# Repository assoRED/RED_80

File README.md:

# RED_80 computer

Currently **work in progress.**

# Repository content

# BOM

 - CMOS z80 CPU
 - AS6c62256 32k*8bits CMOS low power SRAM
 - CMOS 4011 quad NAND logic gate
 - CMOS 4071 quad OR logic gate
 - CMOS 40106 hex trigger
 - 1x tactile switch
 - 3x poalized electrolytic 0.01uF capacitor
 - 2x ceramic (unpolarized) 22pF capactitor
 - Crystal (freq. TBD)
 - 1x 10k resistror
 - 1x 1M resistor
 
# Memory map

| memory address | Usage |
|       :---:    |  :---:  |
|`0x0000` - `0x1FFF`|ROM |
|`0x2000` - `0x3FFF`|EXT ROM| 
|`0x8000` - `0xFFFF`|RAM |

# ROM content

 - `0x0000` system reset/init
 - memroy monitor
 
 # Serial interface
 
 System has been designed to be interfaced with a French Minitel 1B made by MATRA communication terminal.
 
 Serial output is slow (by design). Serial interface configuration : 
 
 - 4800 baud
 - 7bit DATA
 - 1bit STOP
 - Even parity
 - No flow control
 
 To be able to use, you need to setup the minitel in the right comunication mode. Do in order
 
 1) `Fonction`+`T`, `A` Activate "Péri-Informatique" mode
 2) `Fonction`+`T`, `E` Deactivate local character echo
 3) `Fonction`+`P`, `4` Set baudrate to 4800

 Minitel interface can be adapted to serial using the [assoRED/MinitelInterface](https://github.com/assoRED/MinitelInterface) circuit

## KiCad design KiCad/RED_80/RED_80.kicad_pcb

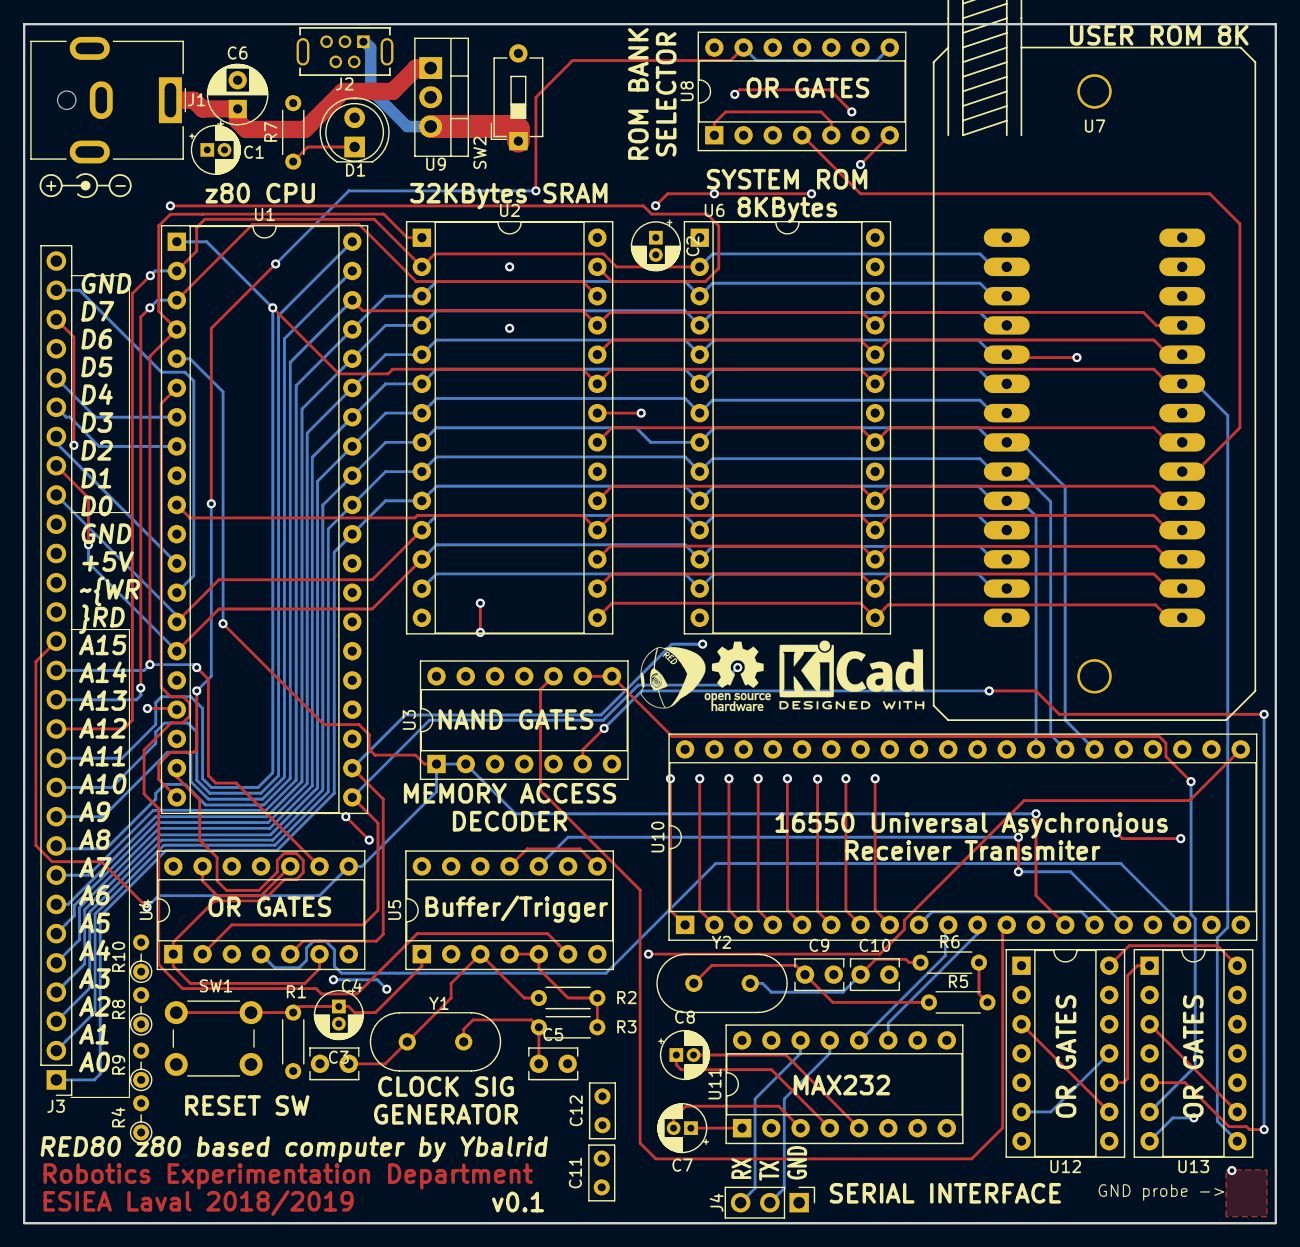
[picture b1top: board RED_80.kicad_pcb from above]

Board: 4 copper layers, 108.7 x 104.1 mm, 44 parts (0 on the bottom side), 78 nets.

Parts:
C1, C2: 0.01uF; CP_Radial_D4.0mm_P1.50mm
C3: 0.01uf; CP_Radial_D4.0mm_P1.50mm
C4, C5, C9, C10: 22pF; C_Rect_L4.0mm_W2.5mm_P2.50mm
C6: 100nf; CP_Radial_D5.0mm_P2.50mm
C7, C8: CP; CP_Radial_D4.0mm_P1.50mm
C11, C12: C; C_Rect_L4.6mm_W2.0mm_P2.50mm_MKS02_FKP02
D1: LED; LED_D5.0mm
J1: Barrel_Jack; BarrelJack_CUI_PJ-063AH_Horizontal
J2: USB_B_Micro; USB_Micro-B_Tensility_54-00023_Vertical
J3: Conn_01x29_Male; PinHeader_1x29_P2.54mm_Vertical
J4: Conn_01x03_Male; PinHeader_1x03_P2.54mm_Vertical
R1: 10k; R_Axial_DIN0204_L3.6mm_D1.6mm_P5.08mm_Horizontal
R2, R5: 1M; R_Axial_DIN0204_L3.6mm_D1.6mm_P5.08mm_Horizontal
R3, R6: R; R_Axial_DIN0204_L3.6mm_D1.6mm_P5.08mm_Horizontal
R4, R8, R9, R10: 100k; R_Axial_DIN0204_L3.6mm_D1.6mm_P2.54mm_Vertical
R7: 180; R_Axial_DIN0204_L3.6mm_D1.6mm_P5.08mm_Horizontal
SW1: RESET_SW; SW_PUSH_6mm_H4.3mm
SW2: SW_SPST; SW_DIP_SPSTx01_Slide_6.7x4.1mm_W7.62mm_P2.54mm_LowProfile
U1: Z80CPU; DIP-40_W15.24mm_Socket
U2: AS6C62256; DIP-28_W15.24mm_Socket
U3: 4011; DIP-14_W7.62mm_Socket
U4, U8: 4071; DIP-14_W7.62mm_Socket
U5: 40106; DIP-14_W7.62mm_Socket
U6: 28C64; DIP-28_W15.24mm_Socket
U7: 28C64; 3M-TEXTOOL-ZIF-DIP-28
U9: L7805; TO-220-3_Vertical
U10: 16550; DIP-40_W15.24mm_Socket
U11: MAX232; DIP-16_W7.62mm_Socket
U12, U13: 4075; DIP-14_W7.62mm_Socket
Y1, Y2: Crystal; Crystal_HC18-U_Vertical

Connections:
/A0: J3.1, U1.30, U2.10, U6.11, U7.11, U10.28
/A1: J3.2, U1.31, U2.9, U6.12, U7.12, U10.27
/A2: J3.3, U1.32, U2.8, U6.13, U7.13, U10.26
/A3: J3.4, U1.33, U2.7, U6.15, U7.15, U12.1
/A4: J3.5, U1.34, U2.6, U6.16, U7.16, U12.2
/A5: J3.6, U1.35, U2.5, U6.17, U7.17, U12.8
/A6: J3.7, U1.36, U2.4, U6.18, U7.18, U12.4
/A7: J3.8, U1.37, U2.3, U6.19, U7.19, U12.5
/A8: J3.9, U1.38, U2.25, U12.12
/A9: J3.10, U1.39, U2.24, U12.13
/A10: J3.11, U1.40, U2.21, U13.2
/A11: J3.12, U1.1, U2.23, U13.8
/A12: J3.13, U1.2, U2.2, U13.4
/A13: J3.14, U1.3, U2.26, U13.5
/A14: J3.15, U1.4, U2.1, U10.13
/A15: J3.16, U1.5, U3.1, U3.2, U10.14
/CPU_BUSRQ: R4.2, U1.25
/CPU_INT: R9.2, U1.16
/CPU_NMI: R10.2, U1.17
/CPU_WAIT: R8.2, U1.24
/D0: J3.21, U1.14, U2.11, U6.10, U7.10, U10.1
/D1: J3.22, U1.15, U2.12, U6.9, U7.9, U10.2
/D2: J3.23, U1.12, U2.13, U6.8, U7.8, U10.3
/D3: J3.24, U1.8, U2.15, U6.7, U7.7, U10.4
/D4: J3.25, U1.7, U2.16, U6.6, U7.6, U10.5
/D5: J3.26, U1.9, U2.17, U6.5, U7.5, U10.6
/D6: J3.27, U1.10, U2.18, U6.4, U7.4, U10.7
/D7: J3.28, U1.13, U2.19, U6.3, U7.3, U10.8
/RED_80_PowerInput/DC+5: J2.1, SW2.1, U9.3
/RED_80_PowerInput/DC_IN: C6.1, J1.1, U9.1
/RED_80_Ram/RAM_ENABLE: U2.20, U3.3
/RED_80_Roms/A8: U6.25, U7.25
/RED_80_Roms/A9: U6.24, U7.24
/RED_80_Roms/A10: U6.21, U7.21
/RED_80_Roms/A11: U6.23, U7.23
/RED_80_Roms/A12: U6.2, U7.2
/RED_80_Roms/USER_ROM_SELECTED: U3.4, U8.6
/RED_80_SERIAL/SERIAL_CLOCK: U5.10, U10.16
CPU_CLK: U1.6, U5.6
GND: C1.2, C2.2, C3.2, C4.2, C5.2, C6.2, C9.2, C10.2, C12.2, J1.2, J2.5, J2.6, J3.20, J3.29, J4.1, R7.2, SW1.2, U1.29, U2.14, U3.7, U4.7, U5.7, U6.14, U6.22, U7.14, U7.22, U8.7, U9.2, U10.19, U10.20, U10.22, U10.25, U11.15, U12.7, U13.7
MAIN_5V: C1.1, C2.1, C11.2, D1.2, J3.19, R1.1, R4.1, R8.1, R9.1, R10.1, SW2.2, U1.11, U2.28, U3.14, U4.14, U5.14, U6.27, U6.28, U7.27, U7.28, U8.14, U10.40, U11.16, U12.14, U13.14
unnamed: C3.1, R1.2, SW1.1, U5.1
unnamed: C4.1, R2.2, U5.3, Y1.1
unnamed: C5.1, R3.2, Y1.2
unnamed: C7.1, U11.1
unnamed: C7.2, U11.3
unnamed: C8.1, U11.4
unnamed: C8.2, U11.5
unnamed: C9.1, R5.2, U5.9, Y2.1
unnamed: C10.1, R6.2, Y2.2
unnamed: C11.1, U11.2
unnamed: C12.1, U11.6
unnamed: D1.1, R7.1
unnamed: R2.1, R3.1, U5.4, U5.5
unnamed: R5.1, R6.1, U5.8, U5.11
unnamed: U1.19, U4.1, U4.6
unnamed: U1.20, U8.8, U8.13
unnamed: U1.21, U4.2, U8.9
unnamed: U1.22, U4.5, U8.12
unnamed: U4.10, U4.13
unnamed: U10.10, U11.12
unnamed: U10.11, U11.11
unnamed: U3.10, U10.12
unnamed: U10.9, U10.15
unnamed: U12.3, U12.9
unnamed: U12.10, U13.1
unnamed: U12.6, U12.11
unnamed: U13.3, U13.9
unnamed: U3.8, U3.9, U13.6
ROM_BANK_ON: U4.11, U8.1, U8.5
RS232_RX: J4.2, U11.13
RS232_TX: J4.3, U11.14
SIG_MRD: J3.17, U2.22, U4.3, U4.12, U10.21
SIG_MWR: J3.18, U2.27, U4.4, U10.18
SIG_RST: U1.26, U5.2
SYS_ROM_ENABLE: U6.20, U8.3
SYS_USER_SELECT: U3.5, U3.6, U8.2
USER_ROM_ENABLE: U7.20, U8.4

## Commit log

2018-09-21 Add empty readme
2018-09-22 fix HEX typo
2018-09-30 Add KiCad files
